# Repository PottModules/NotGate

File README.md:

# Logic Not Gate 

Building Guide <br>
Gerber files  <br>
KiCad files
<br><br>
Der Bau des Moduls erfolgt auf eigenes Risiko. 
Stellt sicher das keine Kurzschlüsse zwischen den Lötpunkten entstehen.
Es wird keine Haftung bei entstehenden Schäden übernommen.

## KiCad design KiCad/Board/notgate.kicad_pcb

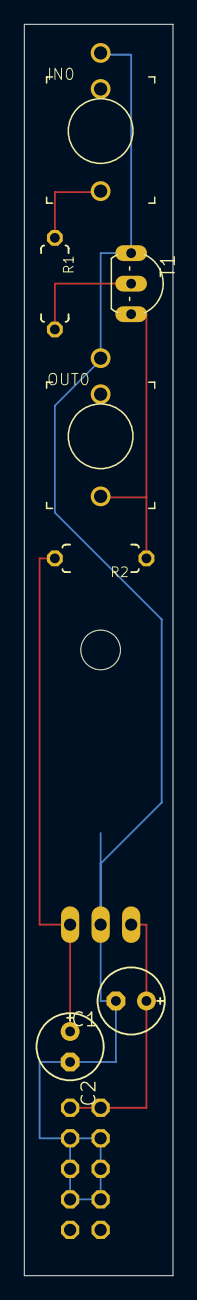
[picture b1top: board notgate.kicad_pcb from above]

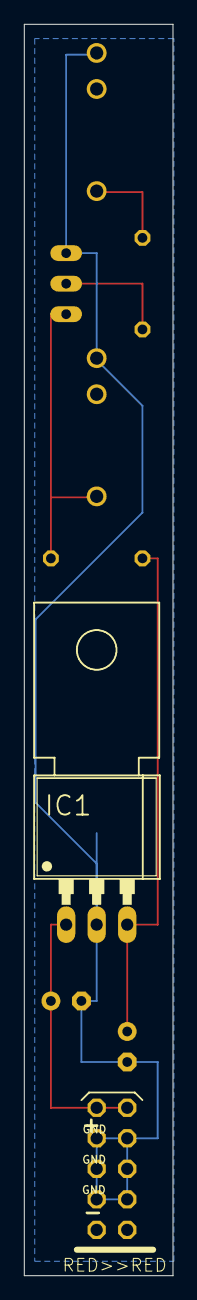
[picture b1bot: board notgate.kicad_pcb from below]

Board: 2 copper layers, 12.4 x 104.1 mm, 9 parts (2 on the bottom side), 6 nets.

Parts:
C1: 10uF; E2,5-6E
C2: 1uF; E2,5-6E
C3: EURO_POWER_LOCKSKINNY; EURO_POWER_HEADER
IC1: 7805; 78MXXL
IN0: THONKICONNNEW; WQP-PJ301M-12_JACK
OUT0: THONKICONNNEW; WQP-PJ301M-12_JACK
R1: 10K; 7MM_RESISTOR
R2: 200R; 7MM_RESISTOR
T1: 2N3904; TO92-EBC

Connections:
0: C1.-, C2.-, C3.3, C3.4, C3.5, C3.6, C3.7, C3.8, IC1.GND, IN0.P$3_SLEEVE, OUT0.P$3_SLEEVE, T1.E
unnamed: R1.2, T1.B
unnamed: OUT0.P$1_TIP, R2.1, T1.C
unnamed: IN0.P$1_TIP, R1.1
unnamed: C1.+, C3.9, C3.10, IC1.IN
VCC: C2.+, IC1.OUT, R2.2

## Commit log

2024-01-02 Create Schematic
2024-01-04 Create files
2024-01-04 Create file
2024-01-04 Create bhsanj
2024-01-04 Create fvghbjn
2024-01-04 Update BOM
